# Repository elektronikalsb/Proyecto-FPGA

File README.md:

# Material didactico sobre programación en Icestudio
En el podréis encontrar un pequeño curso de inciación en porgramación basada en bloques de icestudio, dirigido a personas que se quieren 
iniciar en el mundo de las FPGAs.

El curso consta de teoria con ejemplos y una colección de ejercicios para trabajar la teoria. Todos los ejemplos y ejercicios estarán
resueltos en la colección de bloques que se puede encontrar en la misma carpeta.

</img> </img> </img> 

El objetivo es ir mejorando este curso, añadiendo mejores ejemplos y nuevos ejercicios.

# PacifistaBot

</img> 

Este Kit está pensado para todo aquel que quiera iniciarse en el montaje de robot humanoides. Está diseñado con piezas estandarizadas, baratas, fácil de conseguir y pensado para ser de fácil montaje y programación. Está creado en su totalidad a base de impresión 3D, se programa desde un Arduino Nano o una Alhambra II y usa una placa controladora fácil de soldar.

Hay que destacar que el robot ha sido diseñado por OPRobots y han liberado las fuentes para que cualquiera pueda replicarlo, modificarlo o seguir desarrollándolo. Aunque su diseño inicial esté inspirado en los robots Pacifistas de la serie One Piece, el diseño es totalmente personalizable ya que tanto las manos y la cabeza, como los detalles decorativos de su pecho y piernas son totalmente modificables e intercambiables para conseguir un robot único.

El robot pacifistabot originalmente se ha diseñado para controlado por bluetooth. Partiendo de la idea original se ha modificado creando una nueva versión en la que se puede elegir controlarlo mediante bluetooth o mediante wifi (los 2 a la vez no se puede).

Tambien se ha creado una app movil con la que poder controlarlo via Bluetooth.

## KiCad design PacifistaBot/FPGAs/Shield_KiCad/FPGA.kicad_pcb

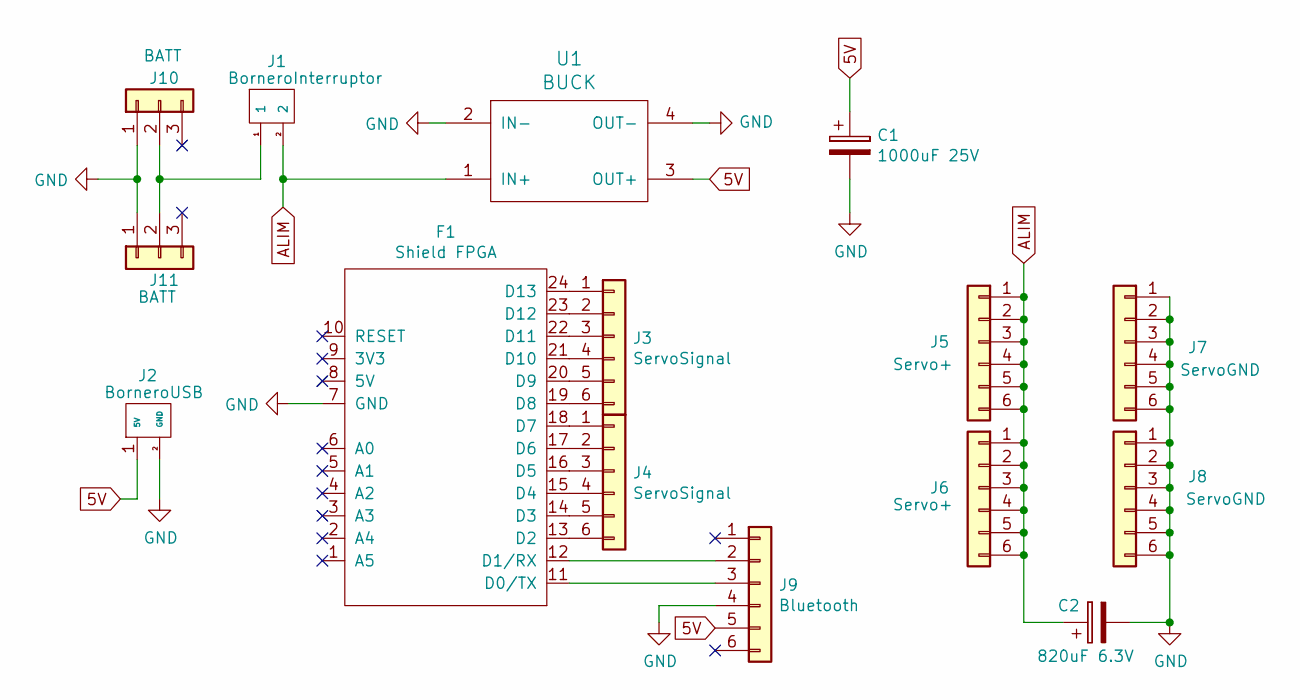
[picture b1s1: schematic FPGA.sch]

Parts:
C1: 1000uF 25V; CP_Radial_D10.0mm_P3.80mm
C2: 820uF 6.3V; CP_Radial_D8.0mm_P3.50mm
F1: Shield FPGA; Shield
J1: BorneroInterruptor; Bornero Interruptor
J2: BorneroUSB; Bornero USB
J3, J4: ServoSignal; Header1x06
J5, J6: Servo+; Header1x06
J7, J8: ServoGND; Header1x06
J9: Bluetooth; Header1x06
J10, J11: BATT; Header1x03
U1: BUCK

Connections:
5V: C1.1, J2.1 (5V), J9.5, U1.3 (OUT+)
ALIM: C2.1, J1.2, J5.1, J5.2, J5.3, J5.4, J5.5, J5.6, J6.1, J6.2, J6.3, J6.4, J6.5, J6.6, U1.1 (IN+)
GND: C1.2, C2.2, F1.7 (GND), J2.2 (GND), J7.1, J7.2, J7.3, J7.4, J7.5, J7.6, J8.1, J8.2, J8.3, J8.4, J8.5, J8.6, J9.4, J10.1, J11.1, U1.2 (IN-), U1.4 (OUT-)
unnamed: F1.11 (D0/TX), J9.3
unnamed: F1.12 (D1/RX), J9.2
unnamed: F1.13 (D2), J4.6
unnamed: F1.14 (D3), J4.5
unnamed: F1.15 (D4), J4.4
unnamed: F1.16 (D5), J4.3
unnamed: F1.17 (D6), J4.2
unnamed: F1.18 (D7), J4.1
unnamed: F1.19 (D8), J3.6
unnamed: F1.20 (D9), J3.5
unnamed: F1.21 (D10), J3.4
unnamed: F1.22 (D11), J3.3
unnamed: F1.23 (D12), J3.2
unnamed: F1.24 (D13), J3.1
unnamed: J1.1, J10.2, J11.2

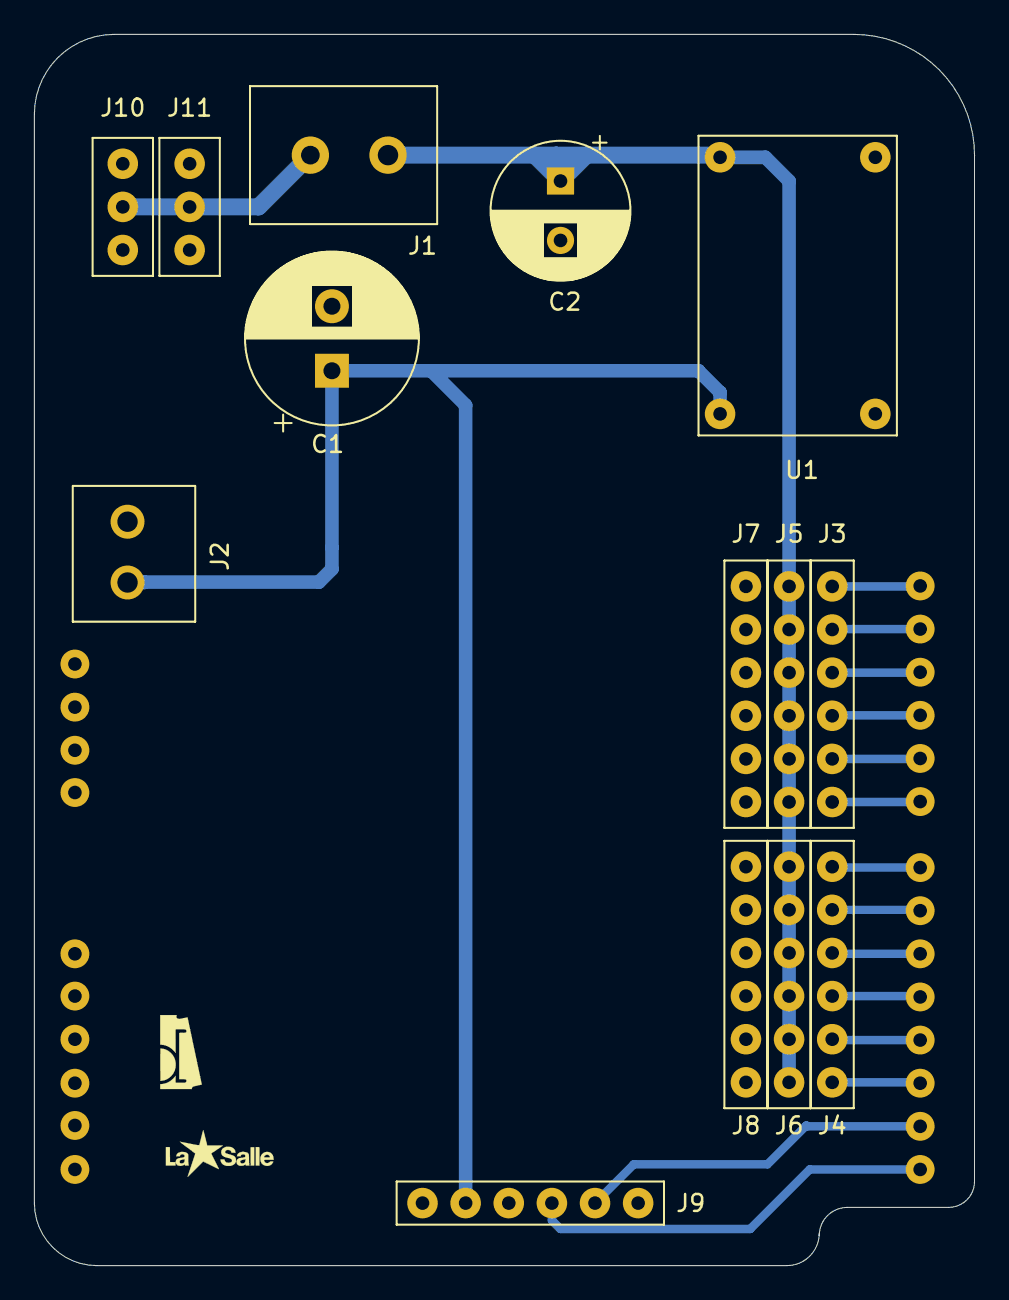
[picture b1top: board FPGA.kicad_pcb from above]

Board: 2 copper layers, 55.4 x 72.5 mm, 15 parts (0 on the bottom side), 18 nets.

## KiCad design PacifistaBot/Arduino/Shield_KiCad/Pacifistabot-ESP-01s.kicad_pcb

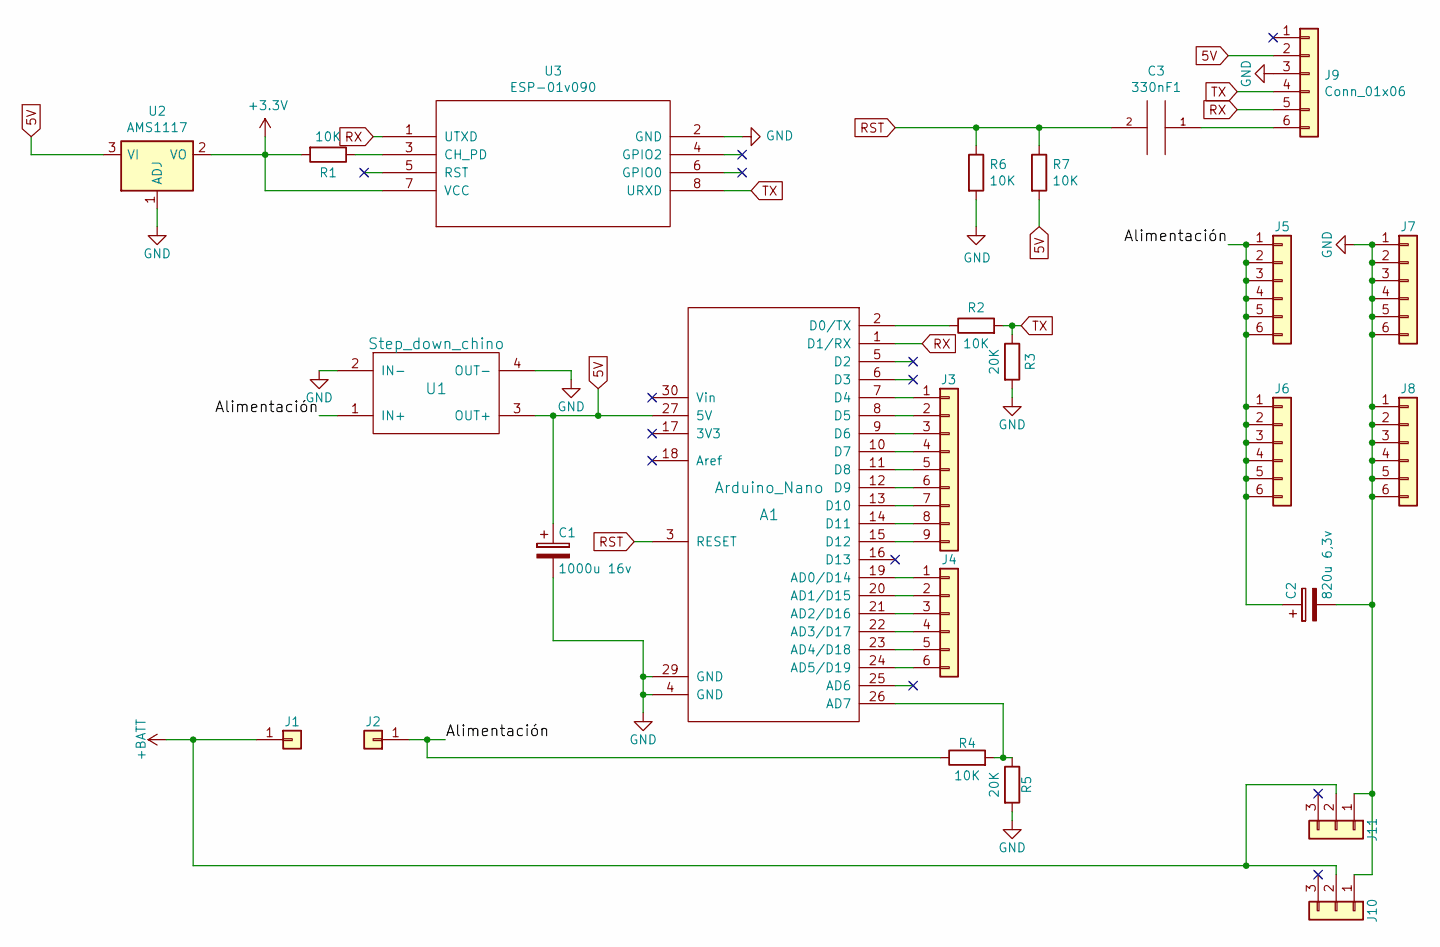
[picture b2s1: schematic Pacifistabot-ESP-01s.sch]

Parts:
A1: Arduino_Nano; arduino_nano
C1: 1000u 16v; CP_Radial_D8.0mm_P3.80mm
C2: 820u 6,3v; CP_Radial_D10.0mm_P5.00mm
C3: 330nF1; C_1206_3216Metric_Pad1.42x1.75mm_HandSolder
J1, J2: Conn_01x01; SolderWirePad_single_1-5mmDrill
J3: Conn_01x09; PinHeader_1x09_P2.54mm_Vertical
J4, J5, J6, J7, J8: Conn_01x06; Pin_Header_Straight_1x06_Pitch2.54mm
J9: Conn_01x06; PinSocket_1x06_P2.54mm_Vertical
J10, J11: Conn_01x03; Pin_Header_Straight_1x03_Pitch2.54mm
R1, R6, R7: 10K; R_1206_3216Metric_Pad1.42x1.75mm_HandSolder
R2, R4: 10K; R_Axial_DIN0207_L6.3mm_D2.5mm_P7.62mm_Horizontal
R3, R5: 20K; R_Axial_DIN0207_L6.3mm_D2.5mm_P7.62mm_Horizontal
U1: Step_down_chino
U2: AMS1117; SOT-223-3_TabPin2
U3: ESP-01v090; PinHeader_2x04_P2.54mm_Vertical

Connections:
5V: A1.27 (5V), C1.1, J9.2, R7.2, U1.3 (OUT+), U2.3 (VI)
+3V3: R1.2, U2.2 (VO), U3.7 (VCC)
+BATT: J1.1, J10.2, J11.2
/Alimentación: C2.1, J2.1, J5.1, J5.2, J5.3, J5.4, J5.5, J5.6, J6.1, J6.2, J6.3, J6.4, J6.5, J6.6, R4.1, U1.1 (IN+)
GND: A1.4 (GND), A1.29 (GND), C1.2, C2.2, J7.1, J7.2, J7.3, J7.4, J7.5, J7.6, J8.1, J8.2, J8.3, J8.4, J8.5, J8.6, J9.3, J10.1, J11.1, R3.2, R5.2, R6.2, U1.2 (IN-), U1.4 (OUT-), U2.1 (ADJ), U3.2 (GND)
unnamed: A1.2 (D0/TX), R2.1
unnamed: A1.7 (D4), J3.1
unnamed: A1.8 (D5), J3.2
unnamed: A1.9 (D6), J3.3
unnamed: A1.10 (D7), J3.4
unnamed: A1.11 (D8), J3.5
unnamed: A1.12 (D9), J3.6
unnamed: A1.13 (D10), J3.7
unnamed: A1.14 (D11), J3.8
unnamed: A1.15 (D12), J3.9
unnamed: A1.19 (AD0/D14), J4.1
unnamed: A1.20 (AD1/D15), J4.2
unnamed: A1.21 (AD2/D16), J4.3
unnamed: A1.22 (AD3/D17), J4.4
unnamed: A1.23 (AD4/D18), J4.5
unnamed: A1.24 (AD5/D19), J4.6
unnamed: A1.26 (AD7), R4.2, R5.1
unnamed: C3.1, J9.6
unnamed: R1.1, U3.3 (CH_PD)
RST: A1.3 (RESET), C3.2, R6.1, R7.1
RX: A1.1 (D1/RX), J9.5, U3.1 (UTXD)
TX: J9.4, R2.2, R3.1, U3.8 (URXD)

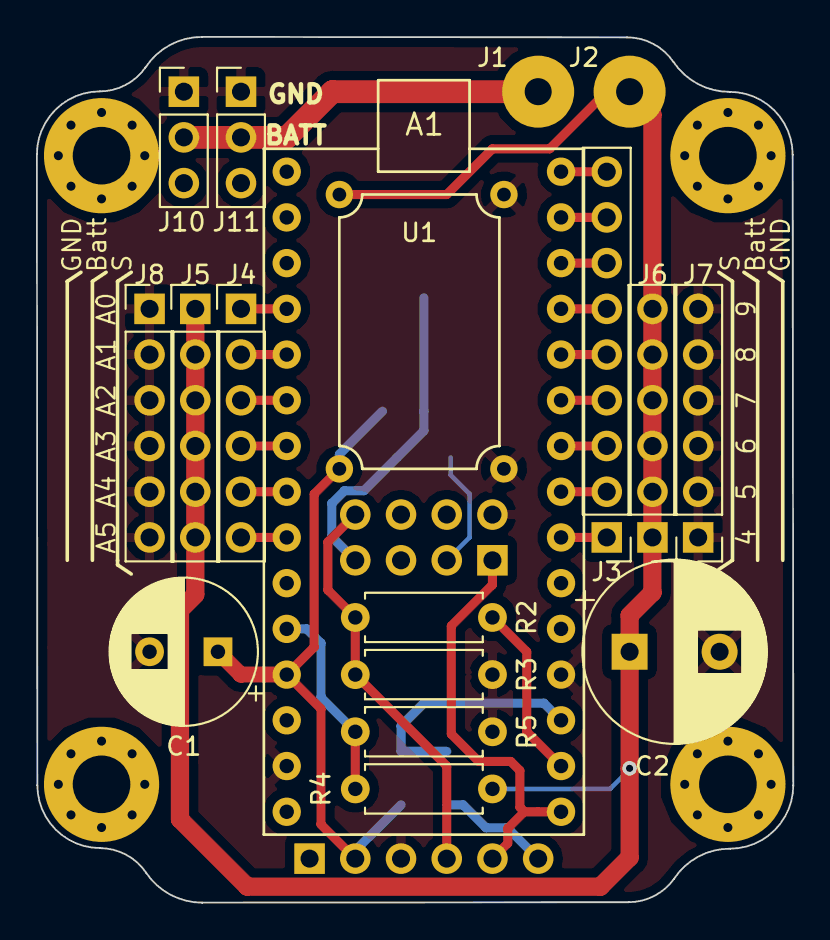
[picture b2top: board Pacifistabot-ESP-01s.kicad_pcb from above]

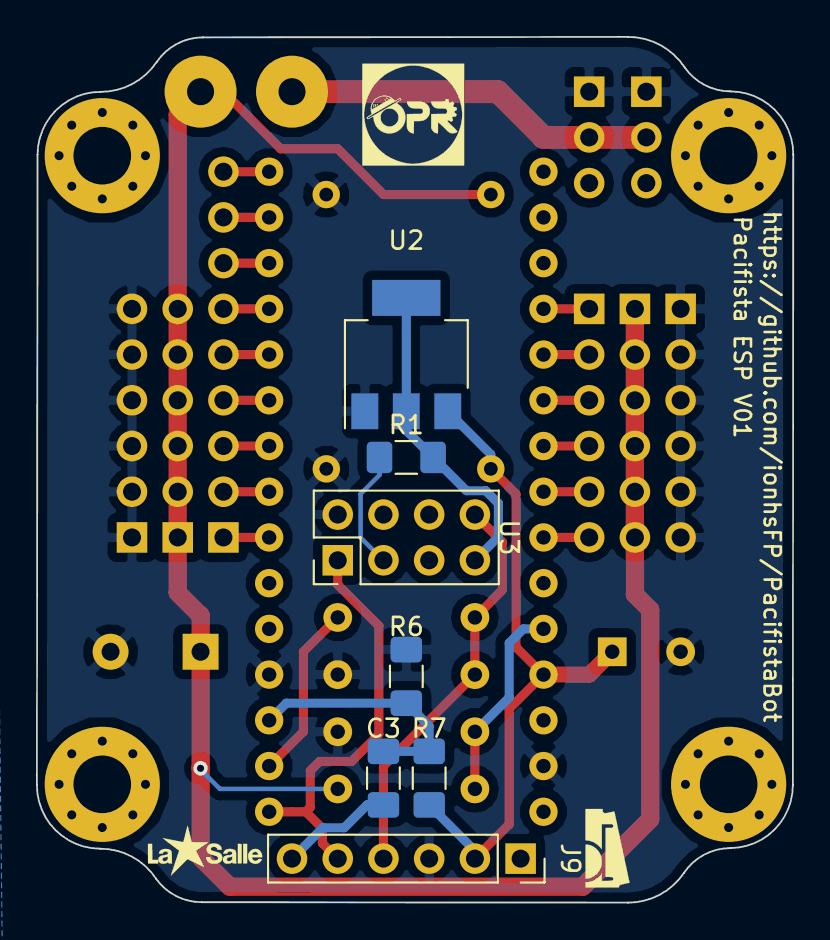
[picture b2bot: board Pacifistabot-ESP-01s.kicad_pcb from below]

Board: 2 copper layers, 42.0 x 48.1 mm, 25 parts (7 on the bottom side), 27 nets.

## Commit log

2020-06-17 Findecurso19_20
